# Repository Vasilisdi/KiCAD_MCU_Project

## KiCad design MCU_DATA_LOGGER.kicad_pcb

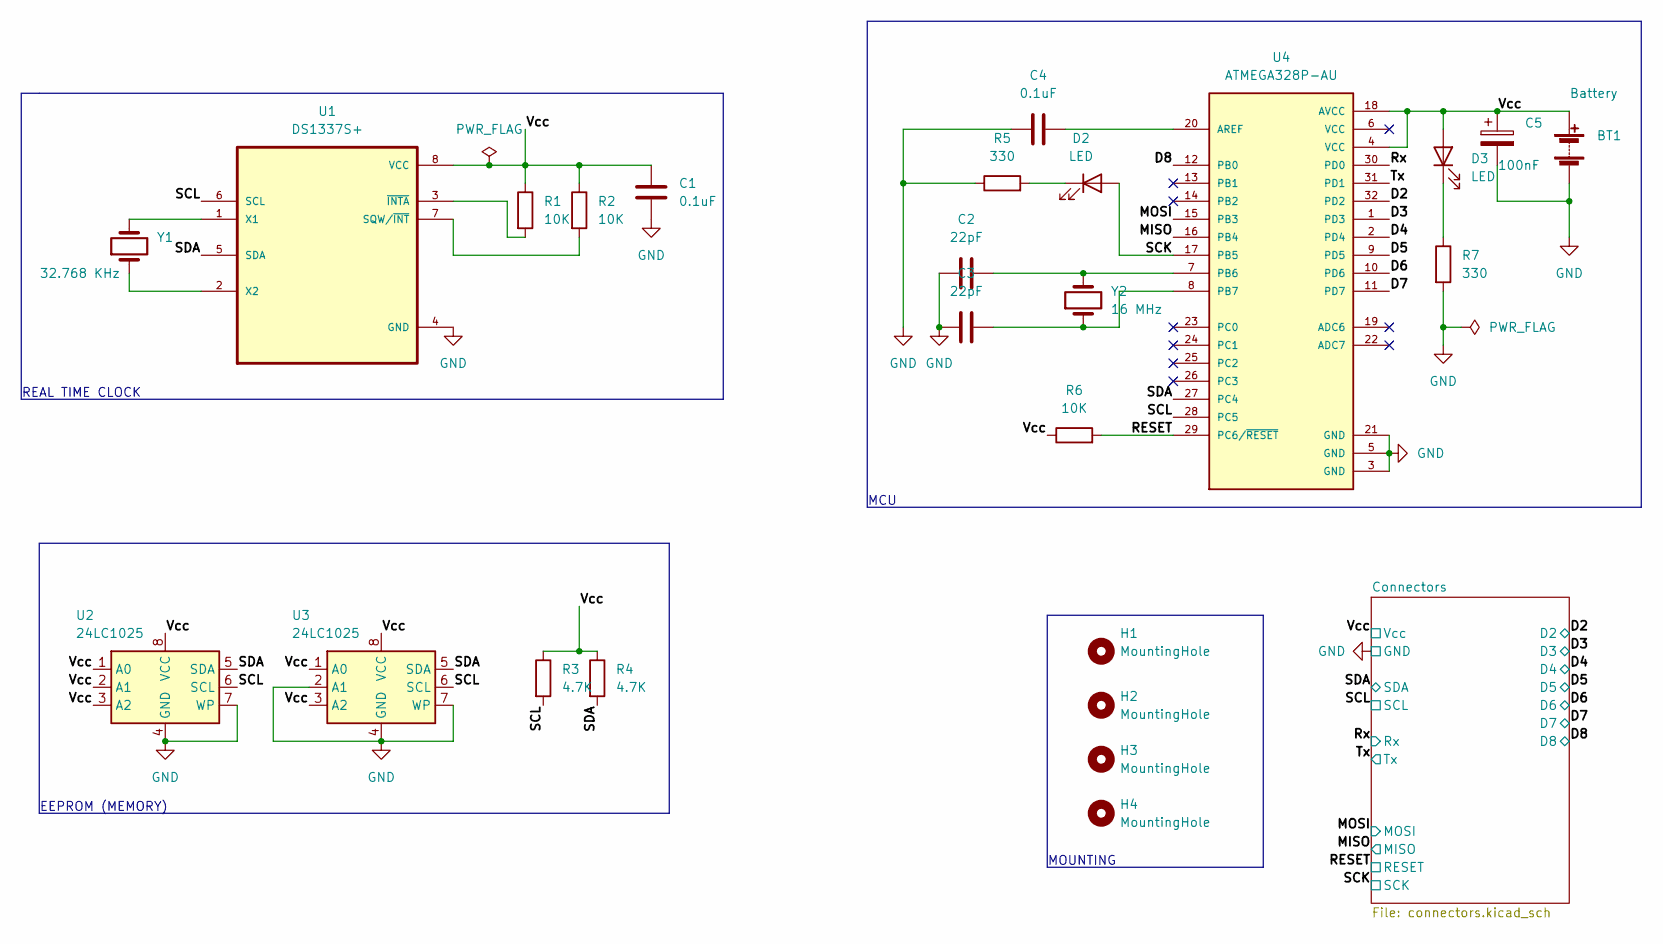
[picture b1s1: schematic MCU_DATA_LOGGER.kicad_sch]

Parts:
BT1: Battery; PinHeader_1x02_P2.54mm_Vertical
C1, C4: 0.1uF; C_0805_2012Metric
C2, C3: 22pF; C_0805_2012Metric
C5: 100nF; C_0805_2012Metric
D2, D3: LED; LED_0805_2012Metric
H1, H2, H3, H4: MountingHole; MountingHole_2.1mm
R1, R2, R6: 10K; R_0805_2012Metric
R3, R4: 4.7K; R_0805_2012Metric
R5, R7: 330; R_0805_2012Metric
U1: DS1337S+; SOIC127P600X175-8N
U2, U3: 24LC1025; SOIC-8_5.23x5.23mm_P1.27mm
U4: ATMEGA328P-AU; QFP80P900X900X120-32N
Y1: 32.768 KHz; Crystal_SMD_5032-2Pin_5.0x3.2mm_HandSoldering
Y2: 16 MHz; Crystal_SMD_5032-2Pin_5.0x3.2mm_HandSoldering

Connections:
/D2: U4.32 (PD2); also elsewhere on the board
/D3: U4.1 (PD3); also elsewhere on the board
/D4: U4.2 (PD4); also elsewhere on the board
/D5: U4.9 (PD5); also elsewhere on the board
/D6: U4.10 (PD6); also elsewhere on the board
/D7: U4.11 (PD7); also elsewhere on the board
/D8: U4.12 (PB0); also elsewhere on the board
/MISO: U4.16 (PB4); also elsewhere on the board
/MOSI: U4.15 (PB3); also elsewhere on the board
/RESET: R6.2, U4.29 (PC6/~RESET); also elsewhere on the board
/Rx: U4.30 (PD0); also elsewhere on the board
/SCK: D2.2 (A), U4.17 (PB5); also elsewhere on the board
/SCL: R3.2, U1.6 (SCL), U2.6 (SCL), U3.6 (SCL), U4.28 (PC5); also elsewhere on the board
/SDA: R4.2, U1.5 (SDA), U2.5 (SDA), U3.5 (SDA), U4.27 (PC4); also elsewhere on the board
/Tx: U4.31 (PD1); also elsewhere on the board
/Vcc: BT1.1 (+), C1.1, C5.1, D3.2 (A), R1.1, R2.1, R3.1, R4.1, R6.1, U1.8 (VCC), U2.1 (A0), U2.2 (A1), U2.3 (A2), U2.8 (VCC), U3.1 (A0), U3.3 (A2), U3.8 (VCC), U4.4 (VCC), U4.18 (AVCC); also elsewhere on the board
GND: BT1.2 (-), C1.2, C2.1, C3.1, C4.1, C5.2, R5.1, R7.2, U1.4 (GND), U2.4 (GND), U2.7 (WP), U3.2 (A1), U3.4 (GND), U3.7 (WP), U4.3 (GND), U4.5 (GND), U4.21 (GND); also elsewhere on the board
unnamed: C2.2, U4.7 (PB6), Y2.2
unnamed: C3.2, U4.8 (PB7), Y2.1
unnamed: C4.2, U4.20 (AREF)
unnamed: D2.1 (K), R5.2
unnamed: D3.1 (K), R7.1
unnamed: R1.2, U1.3 (~INTA)
unnamed: R2.2, U1.7 (SQW/~INT)
unnamed: U1.1 (X1), Y1.2
unnamed: U1.2 (X2), Y1.1

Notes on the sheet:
MOUNTING
REAL TIME CLOCK
EEPROM (MEMORY)
MCU

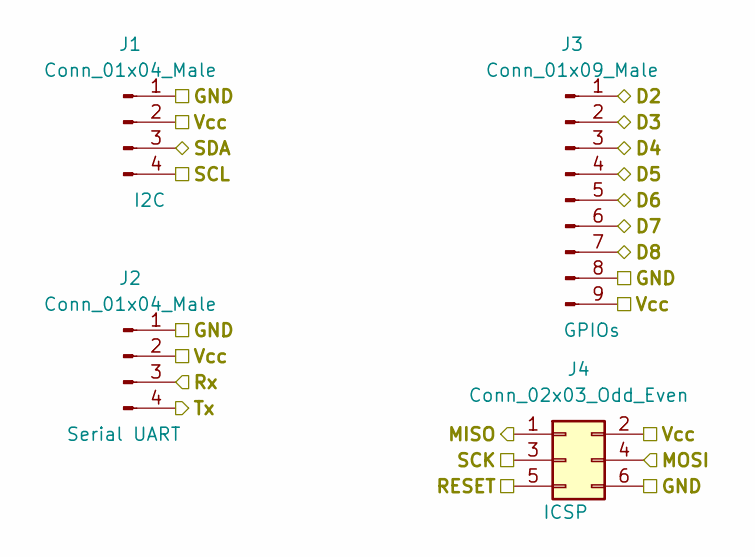
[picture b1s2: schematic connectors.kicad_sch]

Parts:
J1, J2: Conn_01x04_Male; PinHeader_1x04_P2.54mm_Vertical
J3: Conn_01x09_Male; PinHeader_1x09_P2.54mm_Vertical
J4: Conn_02x03_Odd_Even; PinHeader_2x03_P2.54mm_Vertical

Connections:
/D2: J3.1; also elsewhere on the board
/D3: J3.2; also elsewhere on the board
/D4: J3.3; also elsewhere on the board
/D5: J3.4; also elsewhere on the board
/D6: J3.5; also elsewhere on the board
/D7: J3.6; also elsewhere on the board
/D8: J3.7; also elsewhere on the board
/MISO: J4.1; also elsewhere on the board
/MOSI: J4.4; also elsewhere on the board
/RESET: J4.5; also elsewhere on the board
/Rx: J2.3; also elsewhere on the board
/SCK: J4.3; also elsewhere on the board
/SCL: J1.4; also elsewhere on the board
/SDA: J1.3; also elsewhere on the board
/Tx: J2.4; also elsewhere on the board
/Vcc: J1.2, J2.2, J3.9, J4.2; also elsewhere on the board
GND: J1.1, J2.1, J3.8, J4.6; also elsewhere on the board

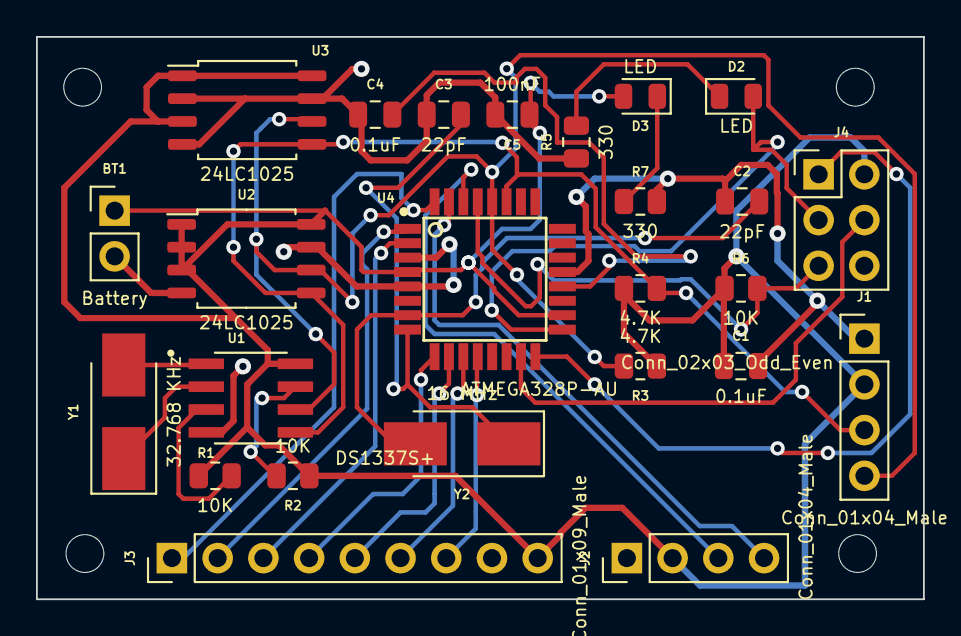
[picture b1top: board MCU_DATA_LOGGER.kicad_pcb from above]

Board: 2 copper layers, 49.3 x 31.2 mm, 29 parts (0 on the bottom side), 26 nets.

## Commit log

2022-04-10 First commit of new repository
2022-04-10 Set up of EEschema
2022-04-10 Have added symbols
2022-04-10 Added components values
2022-04-10 Completed symbol footpring associations
2022-04-11 completed wiring of main sheet
2022-04-11 Completed wiring in all sheets
2022-04-11 Completed schematic
2022-04-11 Setup PCB new.
2022-04-11 Completed placement of footprints
2022-04-13 Routing GND Vcc completed
2022-04-13 Completed routing and Zones
2022-04-13 fixed all issues
2022-04-14 completed
2022-04-15 completed 4 layer
2022-04-15 Completed all + board characteristics
2022-04-15 added gitattributes
2022-04-15 sch modification - correction SCL
2022-04-16 2layer recovery.
2022-04-16 2layer SCL & SCK bug - fix.
2022-04-16 4layer bug fix.
2022-04-21 Final save
